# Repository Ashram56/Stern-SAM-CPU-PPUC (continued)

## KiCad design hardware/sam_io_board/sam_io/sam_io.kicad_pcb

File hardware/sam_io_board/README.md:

# SAM_IO board: PPUC IO board for the Stern SAM IO power driver board

> **Revision 0.2 (branch `claude/sam-io-rp2354-dedicated`): schematic and two routed PCB options.**
> - `sam_io/`: 158 x 100 mm. J13, J3 and J2 sit on the original CPU board harness spots.
> - `sam_io_100mm/`: 100 x 100 mm. J13 on the original spot, J3 3.5 mm lower than the original spot (toward the bottom edge, for room under J2), J2 moved inboard above J3. Same schematic.
>
> Both boards put the bottom-left corner on the CPU board's bottom-left corner, with the KK-396 ramps facing inward.
> On both boards J9 stands on the left edge above J13, turned like the CPU board's J9 (pin 1 at the bottom, odd pins
> and the key notch toward the board centre), so the IO board ribbon arrives from the same side as before.
> The RP2040 and its W25Q flash are replaced by an **RP2354B** (QFN-80, 2 MB internal flash), and a new sheet
> "Dedicated switches" adds the SAM CPU board's harness connectors **J2, J3 and J13** (KK-396) with 17 input
> stages: J3 D9-D16 (flippers, EOS), J13 D17-D24 (tilt, slam, ticket notch, D20, BACK, MINUS, PLUS, SELECT) and
> the coin door memory protect on J2 pin 10. The coin slots (J2 D1-D8) are not routed. The SWD header J3 is
> renamed J20. Details: [`DESIGN.md` section 0](DESIGN.md#0-revision-02-rp2354b-and-dedicated-switches). The
> renders `sam_io/pcb_render.png` and `sam_io_100mm/pcb_render.png` show revision 0.2; the rest of this file still
> describes revision 0.1 (RP2040, 100 x 70 mm PCB).

A PPUC IO board (RP2040 on RS485) that drives a Stern SAM IO power driver board (520-5249-00) through its
CPU connector J1. It is the hardware for the `SAM_IO` board type (`PPUC_BOARD_TYPE=5`) in the io-boards
firmware (Ashram56/io-boards PR #1, `src/IODevices/SamBus/`): one board forwards every coil, flasher and lamp
of the machine to the SAM IO board's registers. It has no switch inputs and no output stage of its own.

It is derived from the PPUC **IO_16_8_1** board, version 1.1.1, by foenich
(<https://github.com/PPUC/Hardware_IO_16_8_1>, commit `46e0c47`), licensed under the
**TAPR Open Hardware License 1.0**. See [Licence](#licence-and-change-notice) below.

- [`DESIGN.md`](DESIGN.md): detailed design notes (circuit, power, reset, bus timing, signal list, BOM, PCB,
  manufacturing, bring-up).
- `sam_io/`: the KiCad 10 project (10.0 file format). Open `sam_io.kicad_pro`.
- `sam_io_100mm/`: the same project with the 100 x 100 mm board (J2 inboard).
- `sam_io_krt/`: an experiment, the same board stripped and routed again from scratch with KiCadRoutingTools,
  with a side-by-side comparison. Not the board to build.
- `sam_io/sam_io_bom.csv`: bill of materials, grouped by value and footprint.
- `sam_io/sam_io.pdf`: the two schematic sheets, for reading without KiCad.
- `sam_io/pcb_render.png`: top view of the routed board; `sam_io/pcb_copper.png`: its copper (F.Cu red, B.Cu blue).
- `original/`: the unmodified IO_16_8_1 v1.1.1 files this design was made from (KiCad 6), its PDF schematic,
  README and change log.
- `tools/`: the scripts that made the changes, for the record (see the end of this file). From now on the
  KiCad files are the source of truth: edit them in KiCad.

## What changed from IO_16_8_1

| | IO_16_8_1 | SAM_IO |
|---|---|---|
| High-power outputs (sheet OUT8) | 8 MOSFET outputs, flyback diodes, F2, 3300 µF C56, J9-J11 | **removed** |
| Inputs (sheet IN16) | 16 inputs with 2N7002 level shifters, J6-J8 | **removed**: GPIO3-18 are the SAM bus |
| SAM bus (new sheet "SAM bus") | | J9 2x10 header, SN74LVC8T245, 74AHCT541, 2N7002 for NBRESET |
| RP2040, flash, crystal, USB-C J4, SWD J3, reset / boot buttons | | unchanged |
| RS485 (ADM3483, J1, JP1-JP3 bias / termination) | | unchanged, except the 0 ohm R9 (RO to GPIO1) is now a track |
| QWIIC J2, its pull-ups R96 / R97 and C8 | | **removed** (2026-10-08) |
| Power J5 (5 V in), AP2112 3.3 V, address DIP SW3 + ladder on GPIO28, LED on GPIO25 | | unchanged |
| Special output (GPIO29 through SN74AHCT1G125 to J5 pin 5) | | unchanged (the SAM_IO firmware does not use it) |

Every part that stays keeps its reference, its position on the board and its routing.

The board is **100 x 70 mm**, the size of the PPUC Opto_16 board (99.7 x 67.3 mm) plus 2.7 mm, because the
address DIP switch SW3 sits that low on IO_16_8_1. The lower 30 mm of IO_16_8_1 held only the output stage.
The four 5.5 mm mounting holes stay at the corners, 5 mm from the edges (the top two did not move, the
bottom two moved up to y = 104 mm). They are not Opto_16's hole pattern.

## Connectors

The kept connectors are the same parts as on IO_16_8_1:

| Ref | Part | Use |
|---|---|---|
| J1 | 6-way RTM push-in terminal | RS485: 1 A, 2 B, 3 SHD, 4 A, 5 B, 6 GND (unchanged) |
| J5 | 6-way RTM push-in terminal | 1, 3, 4 = +5 V in, 2, 6 = GND, 5 = special output (unchanged) |
| J4 | USB-C | programming and debug |
| J3 | 1x3 2.54 mm (not fitted) | SWD |
| **J9** | **2x10 2.54 mm shrouded IDC header** | **SAM bus to the SAM IO board J1** |

J9 is the only new connector. It has the SAM IO board J1 pinout pin for pin, the same as J9 on the SAM CPU
replacement board, so a straight 20-way IDC ribbon (pin 1 to pin 1) connects the two:

| J9 pin | Signal | J9 pin | Signal |
|---|---|---|---|
| 1 | D3 | 2 | D4 |
| 3 | D2 | 4 | D5 |
| 5 | D1 | 6 | D6 |
| 7 | D0 | 8 | D7 |
| 9 | n.c. | 10 | n.c. |
| 11 | n.c. | 12 | A0 |
| 13 | NBRESET (open drain, active low) | 14 | A1 |
| 15 | IOSTB (active low) | 16 | A2 |
| 17 | n.c. | 18 | A3 |
| 19 | GND | 20 | GND |

The SAM IO board's J1 carries no supply, so this board is powered from J5 like every PPUC board.

## SAM bus circuit and GPIO map

The "SAM bus" sheet is a copy of the IO bus sheet of the SAM CPU replacement board
(`hardware/kicad/sam_cpu/io_bus.kicad_sch`, docs/ARCHITECTURE.md 3.1-3.2), so both boards that can drive a
SAM IO board use the same circuit:

- D0-D7: SN74LVC8T245 (U7), A side 3.3 V, B side 5 V. DIR comes from the firmware (1 = this board drives J9),
  10 k pull-down (R28).
- A0-A3 and IOSTB: 74AHCT541 (U8) at 5 V, TTL inputs. Unused inputs tied low.
- Both buffers share BUS_OE_N with a 10 k pull-up (R27): off at power-up, so the SAM IO board's own pull-ups
  hold IOSTB high and nothing latches while the RP2040 boots.
- NBRESET: 2N7002 (Q1) open drain against the SAM IO board's 10 k pull-up. Its gate has a 10 k pull-up (R30),
  so the SAM IO board is held in reset (all outputs off) until the firmware lets go.
- 33 R in series on every J9 line (RN1-RN3, R29), for the ribbon cable.
- Test points TP3 IOSTB, TP4 NBRESET, TP5 D0, TP6 A0.

The GPIOs match `src/IODevices/SamBus/SamBusPins.h` in io-boards exactly, so the firmware needs no change:

| GPIO | Signal | GPIO | Signal |
|---|---|---|---|
| 0, 1, 2 | RS485 TX, RX, DE (unchanged) | 15 | BUS_IOSTB |
| 3-10 | BUS_D0-D7 | 16 | BUS_DIR |
| 11-14 | BUS_A0-A3 | 17 | BUS_OE_N (low = buffers on) |
| 25 | status LED (unchanged) | 18 | NBRESET_DRV (high = SAM IO board in reset) |
| 28 | board id ladder, DIP SW3 (unchanged) | 29 | special output (unchanged) |
| 19-24, 26, 27 | not connected (were Out_1-Out_8) | | |

Revision 0.2 (RP2354B) keeps GPIO0-18, 25 and 29 as above and adds:

| GPIO | Signal | GPIO | Signal |
|---|---|---|---|
| 19-24, 26, 27 | DED_D17-D24 (J13: tilt, slam, ticket notch, D20, BACK, MINUS, PLUS, SELECT) | 38 | MEM_PROTECT (J2 pin 10, coin door) |
| 30-37 | DED_D9-D16 (J3: flipper buttons and EOS) | 40 (ADC0) | board id ladder, DIP SW3 (was GPIO28: the RP2354B's ADC is on GPIO40-47) |
| 28, 39, 41-47 | not connected | | |

All dedicated inputs are active low (switch closed = 0).

## Checks

- ERC (KiCad 10.0.6): 2 errors and 9 warnings, all inherited from IO_16_8_1 (ADC_AVDD and +5 V power-flag
  warnings, +5 V / VCC net name on U5, library symbols that differ from the KiCad 10 libraries). Nothing on the
  new sheet.
- The netlist was compared pin by pin with the original: every kept part keeps its nets, except the RP2040
  GPIO3-18 (now the bus) and GPIO19-24, 26, 27 (now unconnected).
- DRC: fully routed (no unconnected item), no new violation. The remaining items are the original's (USB-C J4
  pad to slot clearance, J2 / C8 courtyards, starved thermals on J4, U5 and C8, footprints that differ from the
  KiCad 10 libraries). Design rules are unchanged: 0.2 mm tracks and clearance, 0.5 / 0.3 mm vias.
- Schematic parity: no net differences. KiCad lists field differences (datasheet links, test point BOM flag)
  that one "Update PCB from Schematic" in KiCad clears.

## Open points

Nothing below blocks reviewing the design; the first group blocks ordering boards, the rest is to check on the
bench or to tidy up later. [DESIGN.md](DESIGN.md) has the details behind each one.

Before ordering:

- **Fabrication files**: no Gerbers, drill files or pick-and-place file yet. Generate them from KiCad (or
  `kicad-cli pcb export gerbers / drill / pos`) once the points below are settled.
- **Update PCB from Schematic**: run it once in KiCad to clear the remaining field differences (datasheet links,
  test point BOM flag). No net changes are expected; re-run DRC afterwards.
- **C31 via in pad**: there was no room for a GND via beside C31 (U7's 5 V decoupling), so its GND pad has
  one. Ask the fab for a filled or tented via, or check the solder joint.
- **Mounting holes**: the four corner holes of the 100 x 70 mm outline follow neither IO_16_8_1 nor Opto_16.
  Check where the board will sit in the machine (or on the SAM IO board's ribbon) and move them if needed.
- **Parts availability**: check stock for the new parts (SN74LVC8T245 in TSSOP-24, 74AHCT541 in TSSOP-20, 2N7002,
  4 x 33 R arrays, 2 x 10 IDC header) at the assembler; the BOM is `sam_io/sam_io_bom.csv`.

On the bench:

- **Bus timing against a real SAM IO board** (ARCHITECTURE.md Q4): setup, IOSTB width and hold as set by the
  firmware (140 / 175 / 245 ns), the STATUS read turnaround (DIR flip and U7 delay inside the read window),
  and edge quality on the 22 pF lines through the series resistors.
- **Watchdog and reset**: the SAM IO board must stay in reset while the RP2040 boots and come out of it only
  once lamp strobes run (DRV0 within 62.5-250 ms); NBRESET held low long enough for the DS1232 (about 20 ms).
- **Ribbon**: the 20-way cable carries only two GND wires; keep it short, check pin-1 orientation on both ends
  and the ground return under full lamp load.
- **5 V supply**: confirm which 5 V the board takes in the machine and that its ground is shared with the SAM
  IO board's logic ground.
- **Firmware**: the `SAM_IO` board type is in Ashram56/io-boards PR #1, still open. Board type `0x05` is a
  proposal to agree with PPUC upstream.

Later, if wanted:

- **References reused**: J9, Q1, R27-R30 and C30-C33 were IO_16_8_1 input / output parts and are now SAM bus
  parts (matching the CPU board's J9). Compare with `original/` by function, not by reference. A re-annotation
  would remove the confusion but break the comparison.
- **Spare resources**: RP2040 GPIO19-24, 26, 27 are unconnected and U8 has three unused channels (inputs tied
  to GND). They could carry the 20 V / 50 V interlock inputs or GI relay control later.
- **Library footprints**: several footprints inherited from IO_16_8_1 differ from the KiCad 10 libraries (DRC
  warnings only). Update them from the library if the board is reworked.
- **Copper tidy-up**: a few short GND tracks between stitching vias on B.Cu are left from IO_16_8_1's routing;
  harmless inside the pour, removable.

## Routing

Two layers, as on IO_16_8_1. The parts that stayed keep their routing; the SAM bus parts sit on the left, where
the input stage was:

- J9 on the left edge, RN1-RN3 and R29 next to it, then U7 (data) above U8 (address and IOSTB), close to the
  RP2040.
- RP2040 to buffers, routed by hand (`tools/c08_bus_fanout.py`). The RP2040 and both buffers number their pins
  anticlockwise, so a bus that keeps its bit order between them has to cross itself once. Each of the 13 lines
  leaves the RP2040 on the top layer (reusing IO_16_8_1's GPIO fanout next to the chip), drops through a via
  under its own buffer pin and crosses under the others on the bottom layer, then comes back up to the pin:
  two vias per line. DIR, OE_N and NBRESET_DRV reuse IO_16_8_1's GPIO16-18 fanout down the right of the RP2040.
- Buffers to J9, pull-ups and power: Freerouting 2.5, with every existing track locked, then a few touch-ups
  (`tools/c09_route_fixes.py`).
- GND is the pour on both layers, as before.

## Licence and change notice

This design is a modification of PPUC IO_16_8_1 v1.1.1 by foenich and is licensed, like the original, under the
**TAPR Open Hardware License 1.0** ([`LICENSE-TAPR-OHL.txt`](LICENSE-TAPR-OHL.txt), an unaltered copy). It is
not covered by the repository's CERN-OHL-S licence. The modifications are licensed under the terms of the TAPR
OHL.

Elements changed (TAPR OHL 4.2a):
- `IO_16_8_1.kicad_sch` -> `sam_io/sam_io.kicad_sch`: IN16 and OUT8 sheets and their labels removed; GPIO3-18
  labels renamed to the SAM bus global labels; no-connect flags on GPIO19-24, 26, 27; "SAM bus" sheet added;
  title block and a change note; file upgraded to KiCad 10.
- `IN16.kicad_sch`, `OUT8.kicad_sch`: removed.
- `sam_io/sam_bus.kicad_sch`: new (from the SAM CPU replacement board's IO bus sheet).
- `IO_16_8_1.kicad_pcb` -> `sam_io/sam_io.kicad_pcb`: IN16 / OUT8 footprints, their tracks and vias, the GNDPWR
  zone and the J6-J11 / fuse silkscreen removed; GND zone extended over the freed area; board name changed to
  "PPUC SAM_IO"; SAM bus parts added and routed; outline cut to 100 x 70 mm, bottom mounting holes, logo and
  board name moved up, copper below the new edge removed; file upgraded to KiCad 10.
- `IO_16_8_1.kicad_pro` -> `sam_io/sam_io.kicad_pro`: renamed, upgraded to KiCad 10.
- `logo.kicad_sym`, `IO_16_8_1.pretty`, `fp-lib-table`, `sym-lib-table`, `PPUC-Logo-PCB-230129.svg`: unchanged.

The original versions of the changed files are in `original/` (TAPR OHL 4.2b). The original documentation names
no licensor e-mail address, so section 3 asks nothing further. Before boards are made, add the Gerber and drill
files to this folder (TAPR OHL 4.2d).

## How the changes were made

`tools/c01_root_sheet.py` and `tools/c02_sam_bus_sheet.py` edited the schematic sheets.
`tools/run.sh` rebuilt the board from the original with `c03_board_update.py` (remove / add footprints, KiCad 10
Python), `c04_board_clean.py` (tracks, zones and silkscreen, on the file text) and `c05_drc_via_cleanup.py`
(leftover vias reported by DRC). `tools/run_route.sh` then made the 100 x 70 mm outline and the routing:
`c06_outline_placement.py` (outline, holes, placement), `c07_trim_copper.py` (copper below the new edge),
`c08_bus_fanout.py` (RP2040 side of the bus), two Freerouting passes (`route_mkdsn.py`, `route_import.py`),
`c09_route_fixes.py` and `c10_silk.py`. Do not rerun them over the current files.

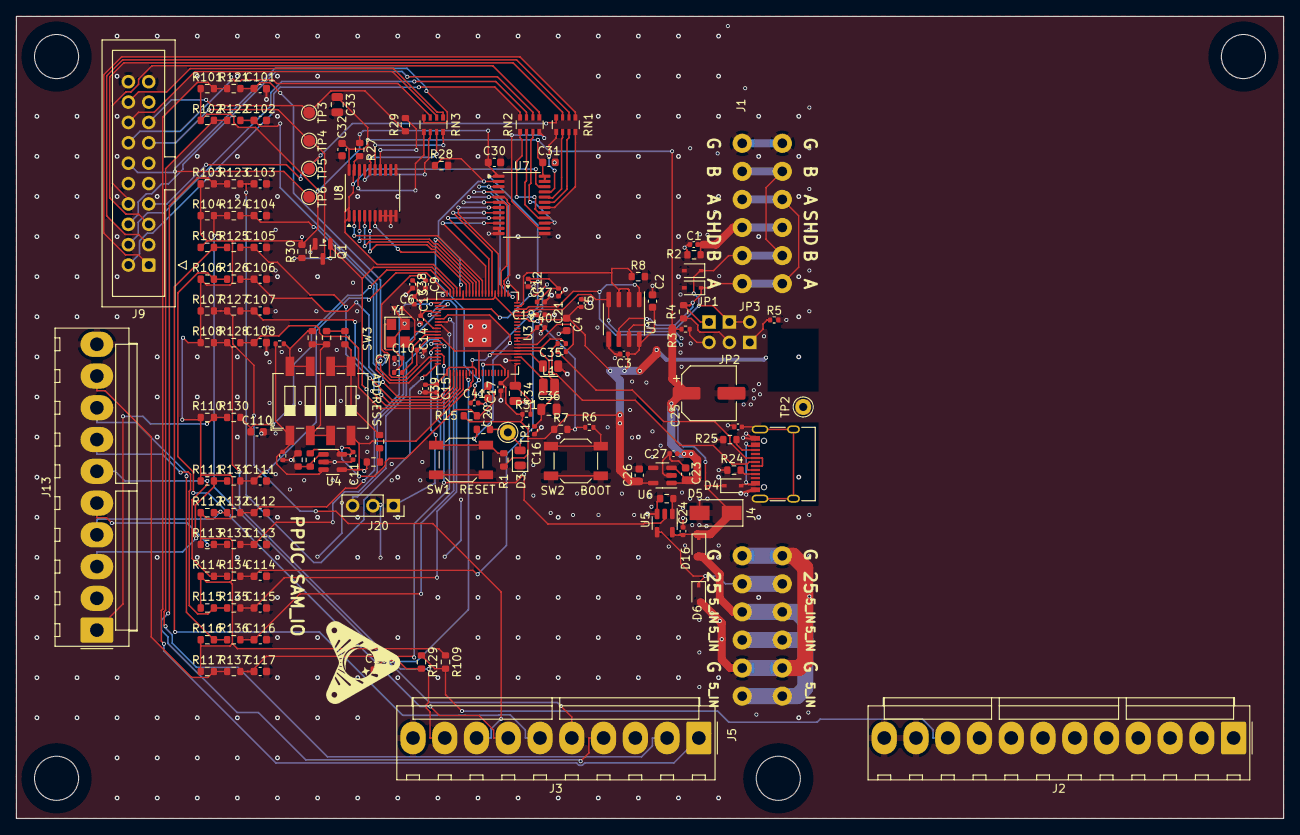
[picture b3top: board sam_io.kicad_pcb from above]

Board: 2 copper layers, 158.0 x 100.0 mm, 158 parts (0 on the bottom side), 123 nets.

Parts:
C1, C3, C5, C9, C10, C11, C12, C13, C14, C15, C17, C19, C22, C24, C27, C37, C38, C39, C40, C41: 100n; C_0402_1005Metric
C2, C4, C20, C23, C26: 10u; C_0603_1608Metric
C6, C7: 27pF; C_0402_1005Metric
C16, C21: 1u; C_0402_1005Metric
C25: 100µ 16V; CP_Elec_6.3x5.4
C30, C31, C32: 100n; C_0603_1608Metric
C33: 10u; C_0805_2012Metric
C34, C35, C36: 4.7u; C_0805_2012Metric
C101, C102, C103, C104, C105, C106, C107, C108, C109, C110, C111, C112, C113, C114, C115, C116, C117: 1n; C_0603_1608Metric
D1, D2: SD15; D_SOD-323
D3: LED gn; LED_0805_2012Metric
D4, D16: 1A; D_SOD-323
D5: SMAJ5.0; D_SMA
D6: SD05; D_SOD-323
J1, J5: Conn_01x06; Terminal_Block_RTMPin
J2: J2 DEDICATED D1-D8; Molex_KK-396_A-41791-0012_1x12_P3.96mm_Vertical
J3: J3 DEDICATED D9-D16; Molex_KK-396_A-41791-0010_1x10_P3.96mm_Vertical
J4: USB_C_Receptacle_USB2.0; USB_C_Receptacle_XKB_U262-16XN-4BVC11
J9: SAM BUS; IDC-Header_2x10_P2.54mm_Vertical
J13: J13 DEDICATED D17-D24; Molex_KK-396_A-41791-0010_1x10_P3.96mm_Vertical
J20: nmount SW Debug; PinSocket_1x03_P2.54mm_Vertical
JP1, JP2, JP3: Jumper_2_Open; PinHeader_1x02_P2.54mm_Vertical
L1: 3.3u; L_Cenker_CKCS201610
Q1: 2N7002; SOT-23
R1, R7, R8, R26, R27, R28, R30, R121, R122, R123, R124, R125, R126, R127, R128, R129, R130, R131, R132, R133, R134, R135, R136, R137: 10k; R_0603_1608Metric
R2, R15: 100R; R_0603_1608Metric
R3, R5: 620; R_0402_1005Metric
R4: 120R; R_0603_1608Metric
R6, R12, R16, R20: 1k; R_0402_1005Metric
R10, R11: 27; R_0402_1005Metric
R13: 33k; R_0603_1608Metric
R14, R18, R19, R23: 2k; R_0603_1608Metric
R17: 5k; R_0603_1608Metric
R21: 470; R_0603_1608Metric
R22: 3k; R_0603_1608Metric
R24, R25: 5k1; R_0603_1608Metric
R29: 33; R_0603_1608Metric
R31: 33; R_0402_1005Metric
R101, R102, R103, R104, R105, R106, R107, R108, R109, R110, R111, R112, R113, R114, R115, R116, R117: 1k; R_0603_1608Metric
RN1, RN2, RN3: 33; R_Array_Convex_4x0603
SW1: Reset; SW_SPST_SKQG_WithStem
SW2: Boot; SW_SPST_SKQG_WithStem
SW3: ADDRESS; SW_DIP_SPSTx04_Slide_6.7x11.72mm_W8.61mm_P2.54mm_LowProfile
TP1: TP_LED; Pin_D1.0mm_L10.0mm
TP2: TP_GND; Pin_D1.0mm_L10.0mm
TP3: J9_IOSTB; TestPoint_Pad_D1.5mm
TP4: J9_NBRESET; TestPoint_Pad_D1.5mm
TP5: J9_D0; TestPoint_Pad_D1.5mm
TP6: J9_A0; TestPoint_Pad_D1.5mm
U1: ADM3483; SOIC-8_3.9x4.9mm_P1.27mm
U3: RP2354B; QFN-80-1EP_10x10mm_P0.4mm_EP3.4x3.4mm
U4: LMV321; SOT-23-5
U5: SN74AHCT1G125; SOT-23-5
U6: AP2112K-3.3; SOT-23-5
U7: SN74LVC8T245; TSSOP-24_4.4x7.8mm_P0.65mm
U8: 74AHCT541; TSSOP-20_4.4x6.5mm_P0.65mm
Y1: 12MHz,18pF; Crystal_SMD_3225-4Pin_3.2x2.5mm

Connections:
+3V3: C2.1, C3.1, C4.1, C5.1, C12.1, C13.1, C14.1, C15.1, C17.1, C19.1, C21.1, C26.1, C30.1, C35.1, C37.1, C38.1, C39.1, C40.1, R1.2, R7.1, R15.1, R27.1, R30.1, R31.1, R101.1, R102.1, R103.1, R104.1, R105.1, R106.1, R107.1, R108.1, R109.1, R110.1, R111.1, R112.1, R113.1, R114.1, R115.1, R116.1, R117.1, U1.8 (VCC), U3.5, U3.15, U3.24, U3.29, U3.41, U3.50, U3.60, U3.64, U3.68, U3.69, U3.76, U6.5 (VOUT), U7.1
+5V: C23.1, C24.1, C25.1, C27.1, C31.1, C32.1, C33.1, D4.1 (K), D5.1 (K), D16.1 (K), R3.1, U5.5 (VCC), U6.1 (VIN), U6.3 (EN), U7.23, U7.24, U8.20
/1V1: C9.1, C10.1, C16.1, C36.1, C41.1, L1.2, U3.10, U3.32, U3.51, U3.65
/3V3A: C11.1, C20.1, R13.1, R15.2, U3.59, U4.5 (V+)
/5V_IN: D16.2 (A), J5.1, J5.3, J5.4
/485_DE: R8.2, U1.2 (~RE), U1.3 (DE), U3.79
/485_RX: U1.1 (RO), U3.78
/485_TX: U1.4 (DI), U3.77
/A: D1.1 (K), J1.1, J1.4, JP1.1 (A), R4.1, U1.6 (A)
/B: D2.1 (K), J1.2, J1.5, JP2.1 (A), JP3.2 (B), U1.7 (B)
/Dedicated switches/IN_D9: J3.1, R101.2, R121.1
/Dedicated switches/IN_D10: J3.2, R102.2, R122.1
/Dedicated switches/IN_D11: J3.4, R103.2, R123.1
/Dedicated switches/IN_D12: J3.5, R104.2, R124.1
/Dedicated switches/IN_D13: J3.6, R105.2, R125.1
/Dedicated switches/IN_D14: J3.7, R106.2, R126.1
/Dedicated switches/IN_D15: J3.8, R107.2, R127.1
/Dedicated switches/IN_D16: J3.9, R108.2, R128.1
/Dedicated switches/IN_D17: J13.1, R110.2, R130.1
/Dedicated switches/IN_D18: J13.3, R111.2, R131.1
/Dedicated switches/IN_D19: J13.4, R112.2, R132.1
/Dedicated switches/IN_D20: J13.5, R113.2, R133.1
/Dedicated switches/IN_D21: J13.6, R114.2, R134.1
/Dedicated switches/IN_D22: J13.7, R115.2, R135.1
/Dedicated switches/IN_D23: J13.8, R116.2, R136.1
/Dedicated switches/IN_D24: J13.9, R117.2, R137.1
/Dedicated switches/IN_MEMPROT: J2.10, R109.2, R129.1
/Out_S: D6.1 (K), J5.5, U5.4
/Out_Special: U3.37, U5.2
/Q_nCS: R6.2, R7.2, U3.75
/SHD: C1.1, J1.3, R2.1
/SWCLK: J20.1, U3.33
/SWDIO: J20.3, U3.34
/USB_D+: J4.A6 (D+), J4.B6 (D+), R10.1
/USB_D-: J4.A7 (D-), J4.B7 (D-), R11.1
/USB_DM_MCU: R11.2, U3.66
/USB_DP_MCU: R10.2, U3.67
/VREG_AVDD: C34.1, R31.2, U3.61
/VREG_LX: L1.1, U3.63
/V_addr: R17.1, SW3.4, U3.49, U4.4
/XIN: C6.2, U3.30, Y1.3
/XOUT: R12.2, U3.31
/nReset: R1.1, SW1.2, U3.35
BUS_A0: U3.9, U8.2
BUS_A1: U3.11, U8.3
BUS_A2: U3.12, U8.4
BUS_A3: U3.13, U8.5
BUS_D0: U3.80, U7.3
BUS_D1: U3.1, U7.4
BUS_D2: U3.2, U7.5
BUS_D3: U3.3, U7.6
BUS_D4: U3.4, U7.7
BUS_D5: U3.6, U7.8
BUS_D6: U3.7, U7.9
BUS_D7: U3.8, U7.10
BUS_DIR: R28.1, U3.16, U7.2
BUS_IOSTB: U3.14, U8.6
BUS_OE_N: R27.2, U3.17, U7.22, U8.1, U8.19
DED_D9: C101.1, R121.2, U3.38
DED_D10: C102.1, R122.2, U3.39
DED_D11: C103.1, R123.2, U3.40
DED_D12: C104.1, R124.2, U3.42
DED_D13: C105.1, R125.2, U3.43
DED_D14: C106.1, R126.2, U3.44
DED_D15: C107.1, R127.2, U3.45
DED_D16: C108.1, R128.2, U3.46
DED_D17: C110.1, R130.2, U3.19
DED_D18: C111.1, R131.2, U3.20
DED_D19: C112.1, R132.2, U3.21
DED_D20: C113.1, R133.2, U3.22
DED_D21: C114.1, R134.2, U3.23
DED_D22: C115.1, R135.2, U3.25
DED_D23: C116.1, R136.2, U3.27
DED_D24: C117.1, R137.2, U3.28
GND: C1.2, C2.2, C3.2, C4.2, C5.2, C6.1, C7.1, C9.2, C10.2, C11.2, C12.2, C13.2, C14.2, C15.2, C16.2, C17.2, C19.2, C20.2, C21.2, C22.2, C23.2, C24.2, C25.2, C26.2, C27.2, C30.2, C31.2, C32.2, C33.2, C34.2, C35.2, C36.2, C37.2, C38.2, C39.2, C40.2, C41.2, C101.2, C102.2, C103.2, C104.2, C105.2, C106.2, C107.2, C108.2, C109.2, C110.2, C111.2, C112.2, C113.2, C114.2, C115.2, C116.2, C117.2, D1.2 (A), D2.2 (A), D3.1 (K), D5.2 (A), D6.2 (A), J1.6, J2.11, J2.12, J3.10, J4.A1 (GND), J4.A12 (GND), J4.B1 (GND), J4.B12 (GND), J5.2, J5.6, J9.19, J9.20, J13.10, J20.2, Q1.2, R2.2, R5.2, R8.1, R14.2, R16.2, R24.2, R25.2, R26.2, R28.2, SW1.1, SW2.1, TP2.1, U1.5 (GND), U3.62, U3.81, U4.2 (V-), U5.3 (GND), U6.2 (GND), U7.11, U7.12, U7.13, U8.7, U8.8, U8.9, U8.10, Y1.2, Y1.4
MEM_PROTECT: C109.1, R129.2, U3.47
NBRESET_DRV: Q1.1, R30.2, U3.18
unnamed: C7.2, R12.1, Y1.1
unnamed: D3.2 (A), R21.2, TP1.1
unnamed: D4.2 (A), J4.A4 (VBUS), J4.A9 (VBUS), J4.B4 (VBUS), J4.B9 (VBUS)
unnamed: J4.A5 (CC1), R24.1
unnamed: J4.B5 (CC2), R25.1
unnamed: C22.1, J4.S1 (SHIELD)
unnamed: J9.1, RN1.1
unnamed: J9.2, RN2.4
unnamed: J9.3, RN1.2
unnamed: J9.4, RN2.3
unnamed: J9.5, RN1.3
unnamed: J9.6, RN2.2
unnamed: J9.7, RN1.4, TP5.1
unnamed: J9.8, RN2.1
unnamed: J9.12, RN3.4, TP6.1
unnamed: J9.13, Q1.3, TP4.1
unnamed: J9.14, RN3.3
unnamed: J9.15, R29.2, TP3.1
unnamed: J9.16, RN3.2
unnamed: J9.18, RN3.1
unnamed: JP1.2 (B), R3.2
unnamed: JP2.2 (B), R4.2
unnamed: JP3.1 (A), R5.1
unnamed: R6.1, SW2.2
unnamed: R17.2, R22.1
unnamed: R18.1, R19.1, SW3.2, SW3.3
unnamed: R18.2, R23.1
unnamed: R19.2, R20.2, SW3.7, SW3.8
unnamed: R22.2, R23.2, SW3.5, SW3.6
unnamed: R26.1, U5.1
unnamed: RN1.8, U7.18
unnamed: RN1.7, U7.19
unnamed: RN1.6, U7.20
unnamed: RN1.5, U7.21
unnamed: RN2.8, U7.14
unnamed: RN2.7, U7.15
unnamed: RN2.6, U7.16
unnamed: RN2.5, U7.17
unnamed: RN3.8, U8.15
unnamed: RN3.7, U8.16
unnamed: RN3.6, U8.17
unnamed: RN3.5, U8.18
unnamed: R21.1, U3.26
unnamed: R13.2, R14.1, U4.1 (+)
unnamed: R16.1, R20.1, SW3.1, U4.3 (-)
unnamed: R29.1, U8.14

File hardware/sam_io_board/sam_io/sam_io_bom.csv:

"Reference","Value","Footprint","QUANTITY","Datasheet"
"C1,C3,C5,C9,C10,C11,C12,C13,C14,C15,C17,C19,C22,C24,C27,C37,C38,C39,C40,C41","100n","Capacitor_SMD:C_0402_1005Metric","20",""
"C2,C4,C20,C23,C26","10u","Capacitor_SMD:C_0603_1608Metric","5",""
"C6,C7","27pF","Capacitor_SMD:C_0402_1005Metric","2",""
"C16,C21","1u","Capacitor_SMD:C_0402_1005Metric","2",""
"C25","100µ 16V","Capacitor_SMD:CP_Elec_6.3x5.4","1",""
"C30,C31,C32","100n","Capacitor_SMD:C_0603_1608Metric","3",""
"C33","10u","Capacitor_SMD:C_0805_2012Metric","1",""
"C34,C35,C36","4.7u","Capacitor_SMD:C_0805_2012Metric","3",""
"C101,C102,C103,C104,C105,C106,C107,C108,C109,C110,C111,C112,C113,C114,C115,C116,C117","1n","Capacitor_SMD:C_0603_1608Metric","17",""
"D1,D2","SD15","Diode_SMD:D_SOD-323","2",""
"D3","LED gn","LED_SMD:LED_0805_2012Metric","1",""
"D4,D16","1A","Diode_SMD:D_SOD-323","2",""
"D5","SMAJ5.0","Diode_SMD:D_SMA","1",""
"D6","SD05","Diode_SMD:D_SOD-323","1",""
"J1,J5","Conn_01x06","IO_16_8_1:Terminal_Block_RTMPin","2",""
"J2","J2 DEDICATED D1-D8","Connector_Molex:Molex_KK-396_A-41791-0012_1x12_P3.96mm_Vertical","1",""
"J3","J3 DEDICATED D9-D16","Connector_Molex:Molex_KK-396_A-41791-0010_1x10_P3.96mm_Vertical","1",""
"J4","USB_C_Receptacle_USB2.0","Connector_USB:USB_C_Receptacle_XKB_U262-16XN-4BVC11","1","https://www.usb.org/sites/default/files/documents/usb_type-c.zip"
"J9","SAM BUS","Connector_IDC:IDC-Header_2x10_P2.54mm_Vertical","1",""
"J13","J13 DEDICATED D17-D24","Connector_Molex:Molex_KK-396_A-41791-0010_1x10_P3.96mm_Vertical","1",""
"JP1,JP2,JP3","Jumper_2_Open","Connector_PinHeader_2.54mm:PinHeader_1x02_P2.54mm_Vertical","3",""
"L1","3.3u","Inductor_SMD:L_Cenker_CKCS201610","1",""
"Q1","2N7002","Package_TO_SOT_SMD:SOT-23","1","https://www.onsemi.com/pub/Collateral/NDS7002A-D.PDF"
"R1,R7,R8,R26,R27,R28,R30,R121,R122,R123,R124,R125,R126,R127,R128,R129,R130,R131,R132,R133,R134,R135,R136,R137","10k","Resistor_SMD:R_0603_1608Metric","24",""
"R2,R15","100R","Resistor_SMD:R_0603_1608Metric","2",""
"R3,R5","620","Resistor_SMD:R_0402_1005Metric","2",""
"R4","120R","Resistor_SMD:R_0603_1608Metric","1",""
"R6,R12,R16,R20","1k","Resistor_SMD:R_0402_1005Metric","4",""
"R10,R11","27","Resistor_SMD:R_0402_1005Metric","2",""
"R13","33k","Resistor_SMD:R_0603_1608Metric","1",""
"R14,R18,R19,R23","2k","Resistor_SMD:R_0603_1608Metric","4",""
"R17","5k","Resistor_SMD:R_0603_1608Metric","1",""
"R21","470","Resistor_SMD:R_0603_1608Metric","1",""
"R22","3k","Resistor_SMD:R_0603_1608Metric","1",""
"R24,R25","5k1","Resistor_SMD:R_0603_1608Metric","2",""
"R29","33","Resistor_SMD:R_0603_1608Metric","1",""
"R31","33","Resistor_SMD:R_0402_1005Metric","1",""
"R101,R102,R103,R104,R105,R106,R107,R108,R109,R110,R111,R112,R113,R114,R115,R116,R117","1k","Resistor_SMD:R_0603_1608Metric","17",""
"RN1,RN2,RN3","33","Resistor_SMD:R_Array_Convex_4x0603","3",""
"SW1","Reset","Button_Switch_SMD:SW_SPST_SKQG_WithStem","1",""
"SW2","Boot","Button_Switch_SMD:SW_SPST_SKQG_WithStem","1",""
"SW3","ADDRESS","Button_Switch_SMD:SW_DIP_SPSTx04_Slide_6.7x11.72mm_W8.61mm_P2.54mm_LowProfile","1",""
"TP3","J9_IOSTB","TestPoint:TestPoint_Pad_D1.5mm","1",""
"TP4","J9_NBRESET","TestPoint:TestPoint_Pad_D1.5mm","1",""
"TP5","J9_D0","TestPoint:TestPoint_Pad_D1.5mm","1",""
"TP6","J9_A0","TestPoint:TestPoint_Pad_D1.5mm","1",""
"U1","ADM3483","Package_SO:SOIC-8_3.9x4.9mm_P1.27mm","1","http://www.icbase.com/pdf/SPX/SPX00480106.pdf"
"U3","RP2354B","Package_DFN_QFN:QFN-80-1EP_10x10mm_P0.4mm_EP3.4x3.4mm","1",""
"U4","LMV321","Package_TO_SOT_SMD:SOT-23-5","1","http://www.ti.com/lit/ds/symlink/lmv324.pdf"
"U5","SN74AHCT1G125","Package_TO_SOT_SMD:SOT-23-5","1","http://www.ti.com/lit/sg/scyt129e/scyt129e.pdf"
"U6","AP2112K-3.3","Package_TO_SOT_SMD:SOT-23-5","1","https://www.diodes.com/assets/Datasheets/AP2112.pdf"
"U7","SN74LVC8T245","Package_SO:TSSOP-24_4.4x7.8mm_P0.65mm","1","https://www.ti.com/lit/ds/symlink/sn74lvc8t245.pdf"
"U8","74AHCT541","Package_SO:TSSOP-20_4.4x6.5mm_P0.65mm","1","https://www.ti.com/lit/ds/symlink/sn74ahct541.pdf"
"Y1","12MHz,18pF","Crystal:Crystal_SMD_3225-4Pin_3.2x2.5mm","1",""
